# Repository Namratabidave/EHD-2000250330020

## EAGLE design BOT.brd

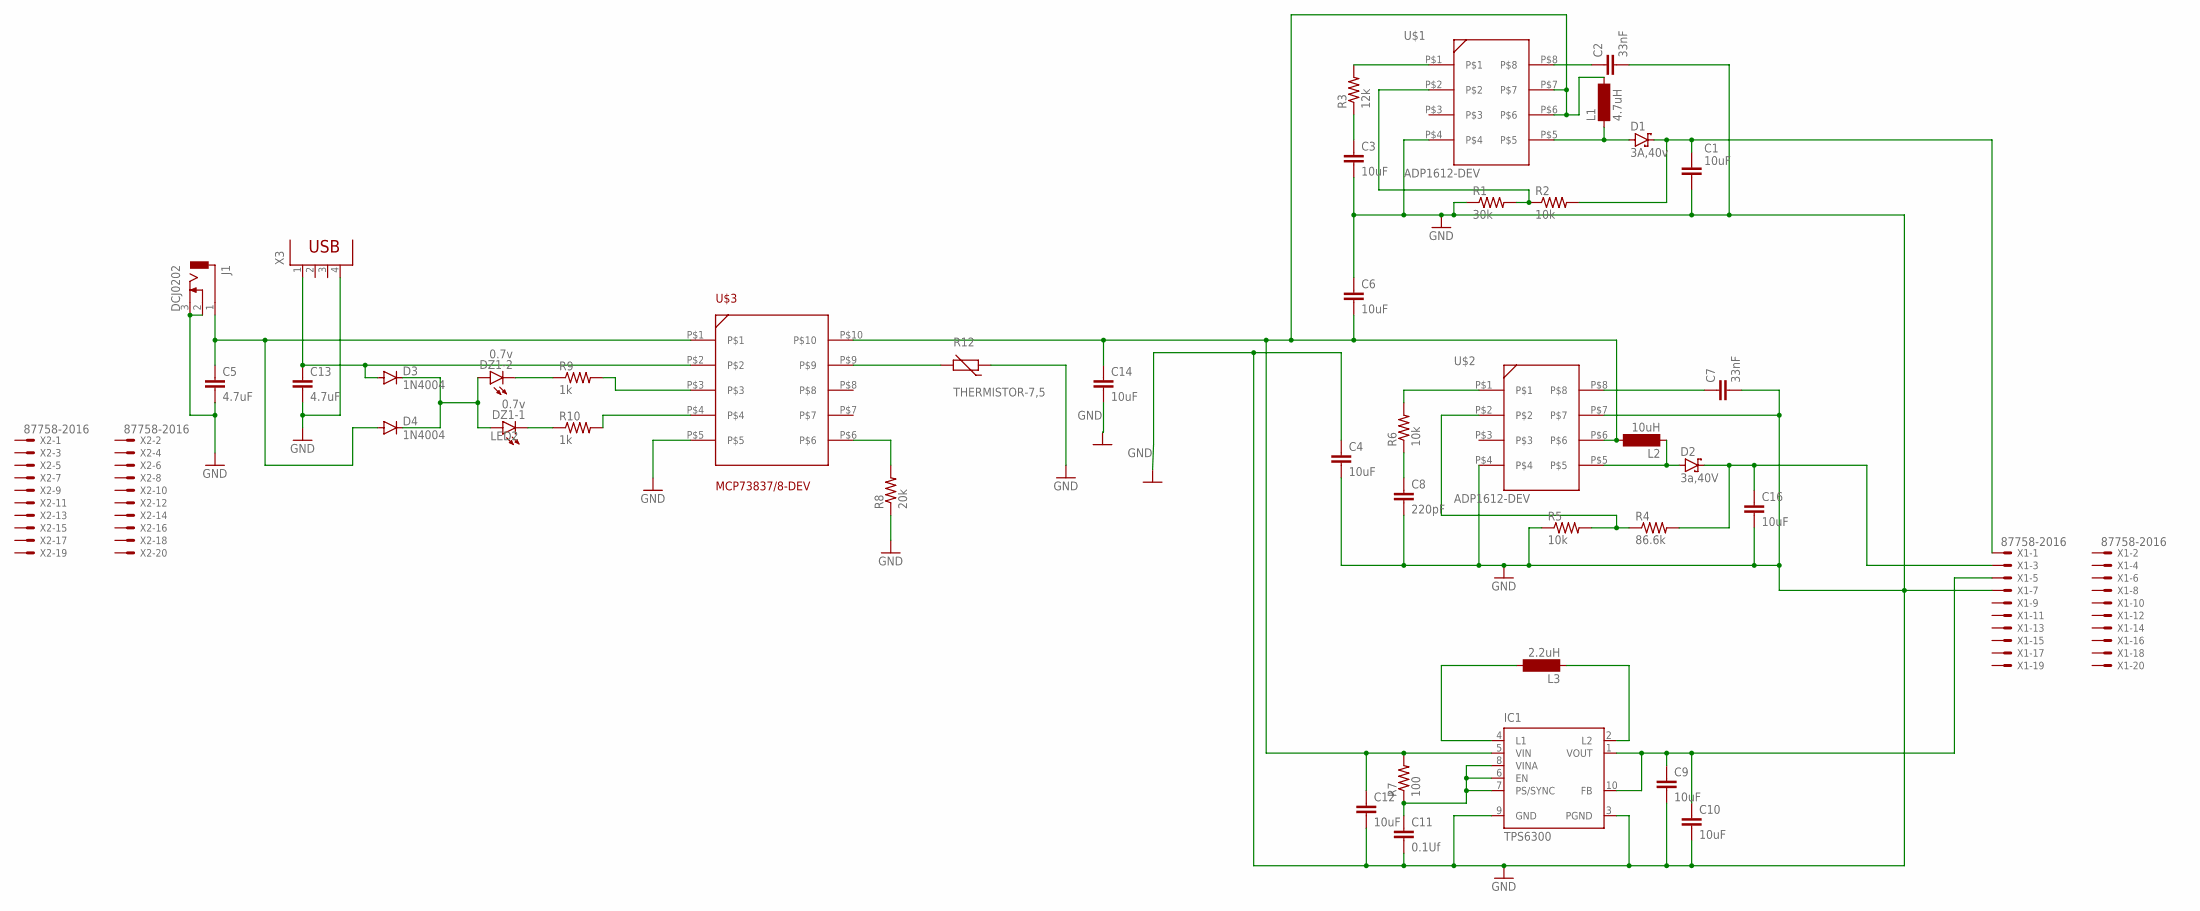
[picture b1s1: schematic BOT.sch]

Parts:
C2: 33nF; C2.5-2
C3, C6, C14: 10uF; C2.5-2
C4, C9, C10, C12, C16: 10uF; C2.5-3
C5, C13: 4.7uF; C2.5-2
C7: 33nF; C2.5-3
C8: 220pF; C2.5-3
C11: 0.1Uf; C2.5-3
D1: 3A,40v; SOD323_ST
D2: 3a,40V; SOD323_ST
D3, D4: 1N4004; DO41-10
DZ1: 0.7v; LZR182
IC1: TPS6300; DRC-S-PVSON-N10
J1: DCJ0202
L1: 4.7uH; SD8
L2: 10uH; SD8
L3: 2.2uH; SD8
R1: 30k; 0204/5
R2, R5, R6: 10k; 0204/5
R3: 12k; 0204/5
R4: 86.6k; 0204/5
R7: 100; 0204/5
R8: 20k; 0204/5
R9, R10: 1k; 0204/5
R12: THERMISTOR-7,5; R-7,5
U$1, U$2: ADP1612-DEV; MSOP-ADP1612
U$3: MCP73837/8-DEV; MSOP-MCP73837/8
X1, X2: 87758-2016
X3: PN87520

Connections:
GND: C2.2, C3.2, C4.1, C4.2, C5.2, C6.1, C7.2, C8.2, C9.2, C10.2, C11.2, C12.2, C13.2, C14.2, C16.2, IC1.3 (PGND), IC1.9 (GND), J1.2, J1.3, R1.1, R5.1, R8.1, R12.1, U$1.P$4, U$2.P$4, U$2.P$7, U$3.P$5, X1.7, X3.4
LED2: D3.C, D4.C, DZ1.A1 (A), DZ1.A2 (A)
unnamed: R3.2, U$1.P$1
unnamed: C3.1, R3.1
unnamed: C2.1, U$1.P$8
unnamed: R8.2, U$3.P$6
unnamed: D1.A, L1.1, U$1.P$5
unnamed: R1.2, R2.1, U$1.P$2
unnamed: R6.2, U$2.P$1
unnamed: D1.C, R2.2, X1.1
unnamed: C8.1, R6.1
unnamed: R9.2, U$3.P$3
unnamed: D2.A, L2.1, U$2.P$5
unnamed: IC1.4 (L1), L3.2
unnamed: C7.1, U$2.P$8
unnamed: R4.1, R5.2, U$2.P$2
unnamed: C16.1, D2.C, R4.2, X1.3
unnamed: IC1.2 (L2), L3.1
unnamed: C9.1, C10.1, IC1.1 (VOUT), IC1.10 (FB), X1.5
unnamed: C6.2, C12.1, C14.1, IC1.5 (VIN), L1.2, L2.2, R7.2, U$1.P$6, U$1.P$7, U$2.P$6, U$3.P$10
unnamed: C11.1, IC1.6 (EN), IC1.7 (PS/SYNC), IC1.8 (VINA), R7.1
unnamed: R12.2, U$3.P$9
unnamed: DZ1.K2 (C), R9.1
unnamed: DZ1.K1 (C), R10.1
unnamed: C5.1, D4.A, J1.1, U$3.P$1
unnamed: R10.2, U$3.P$4
unnamed: C13.1, D3.A, U$3.P$2, X3.1

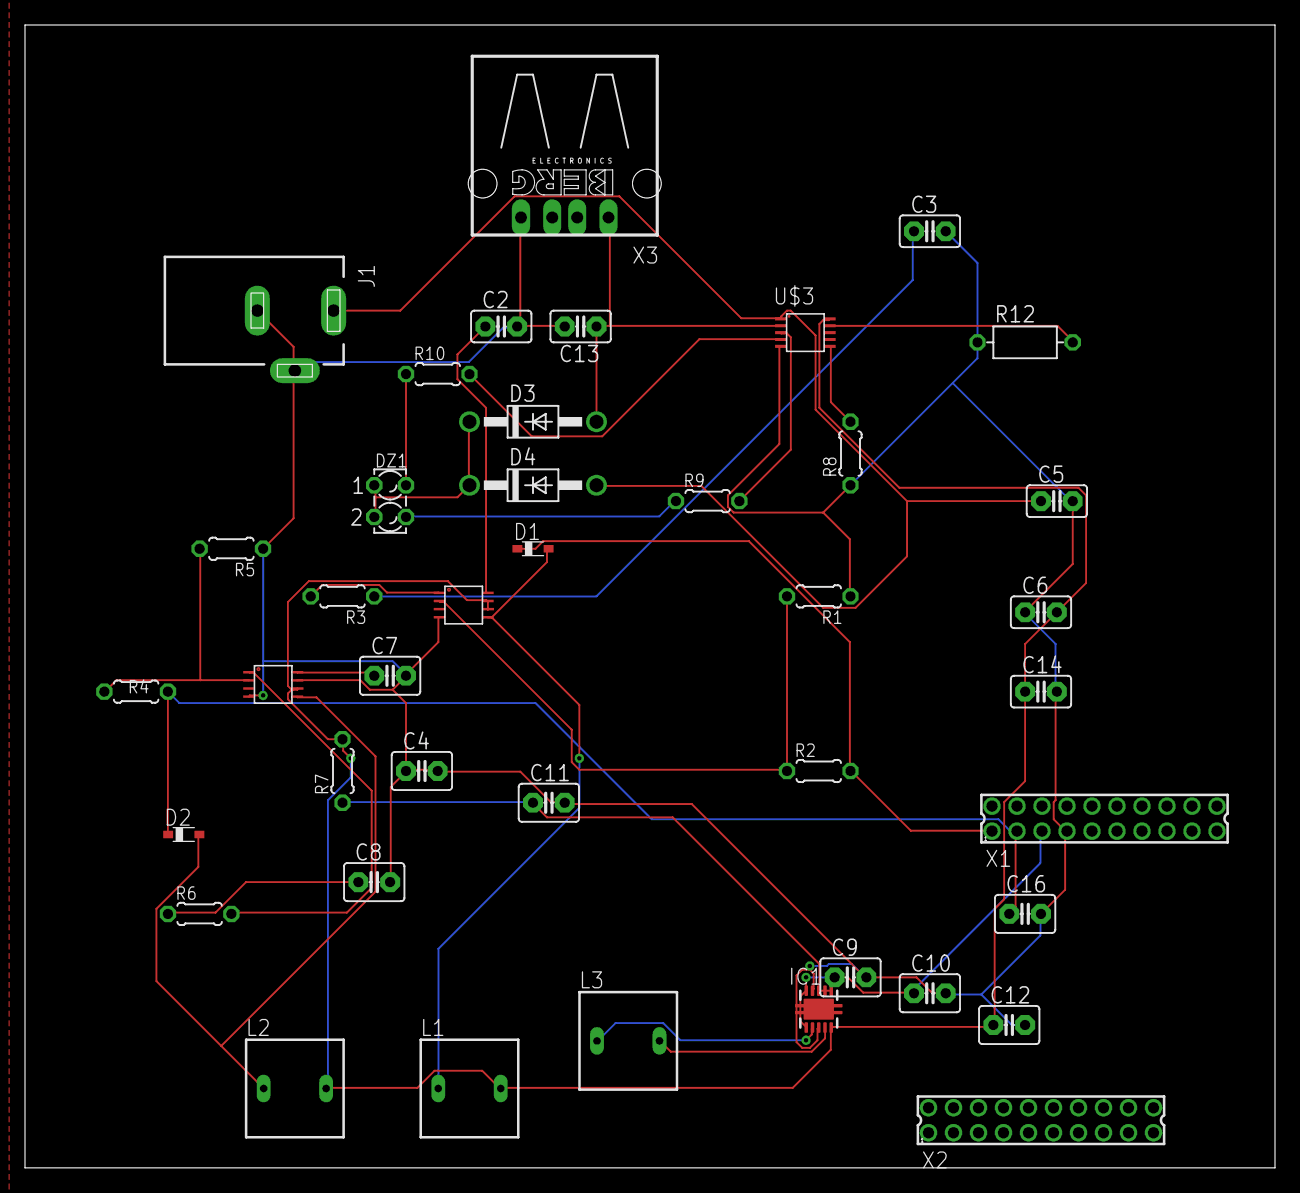
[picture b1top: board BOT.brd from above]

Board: 2 copper layers, 100.0 x 91.4 mm, 41 parts (0 on the bottom side), 27 nets.

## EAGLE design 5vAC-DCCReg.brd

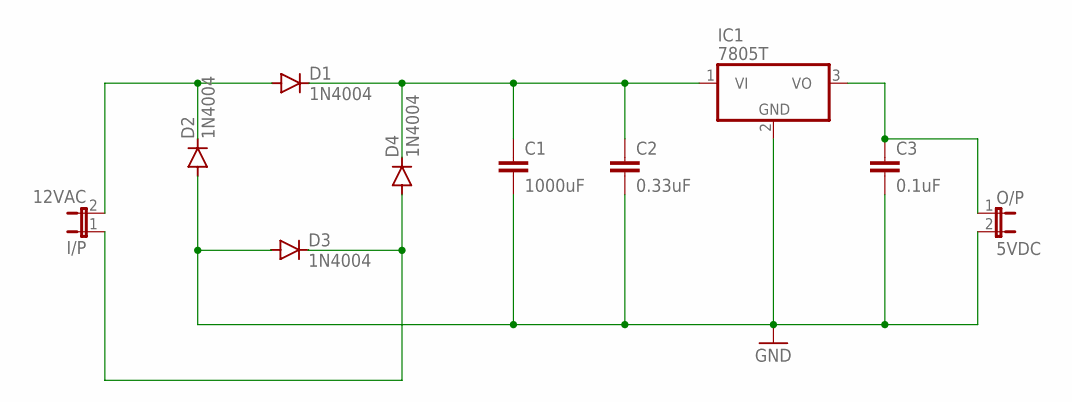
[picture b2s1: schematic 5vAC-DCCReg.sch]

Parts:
C1: 1000uF; C2.5-3
C2: 0.33uF; C2.5-3
C3: 0.1uF; C2.5-3
D1, D2, D3, D4: 1N4004; DO41-10
I/P: 12VAC; JP1
IC1: 7805T; TO220H
O/P: 5VDC; JP1

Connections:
GND: C1.2, C2.2, C3.2, D2.A, D3.A, IC1.2 (GND), O/P.2
unnamed: D1.A, D2.C, I/P.2
unnamed: C1.1, C2.1, D1.C, D4.C, IC1.1 (VI)
unnamed: D3.C, D4.A, I/P.1
unnamed: C3.1, IC1.3 (VO), O/P.1

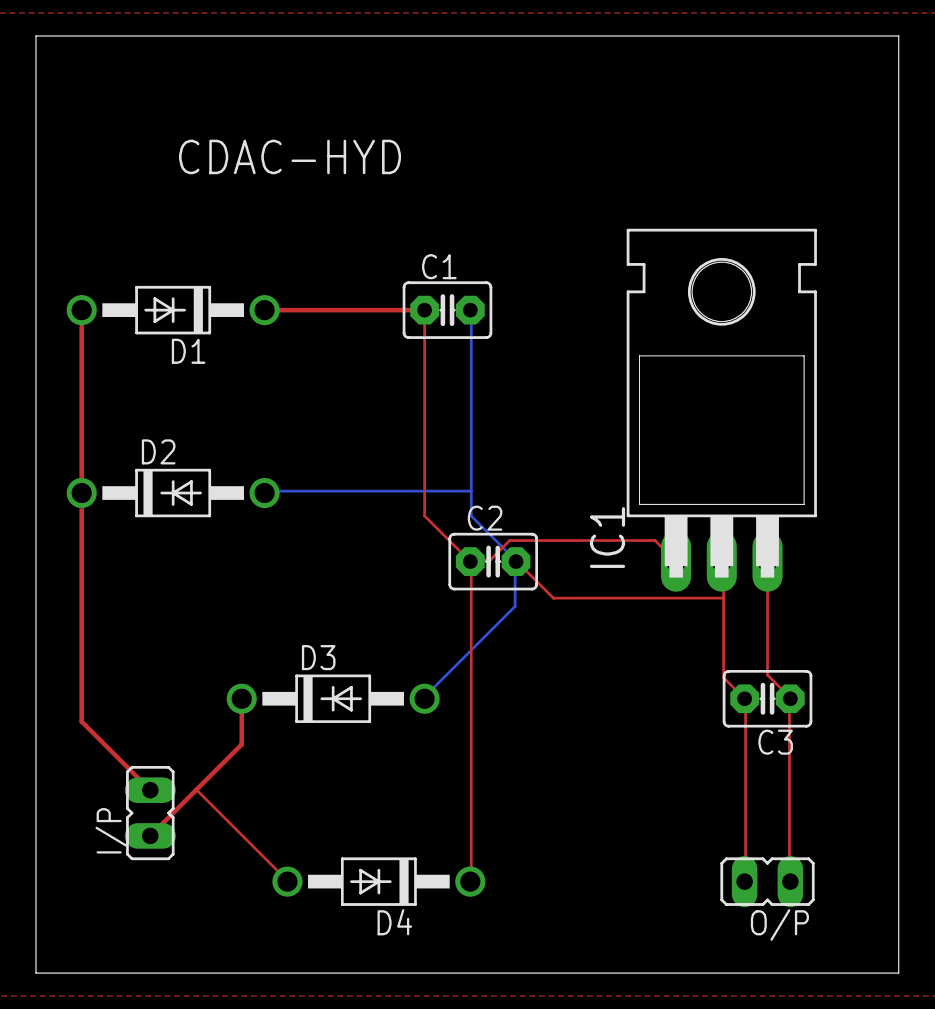
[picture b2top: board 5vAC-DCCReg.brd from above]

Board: 2 copper layers, 47.9 x 52.1 mm, 10 parts (0 on the bottom side), 5 nets.

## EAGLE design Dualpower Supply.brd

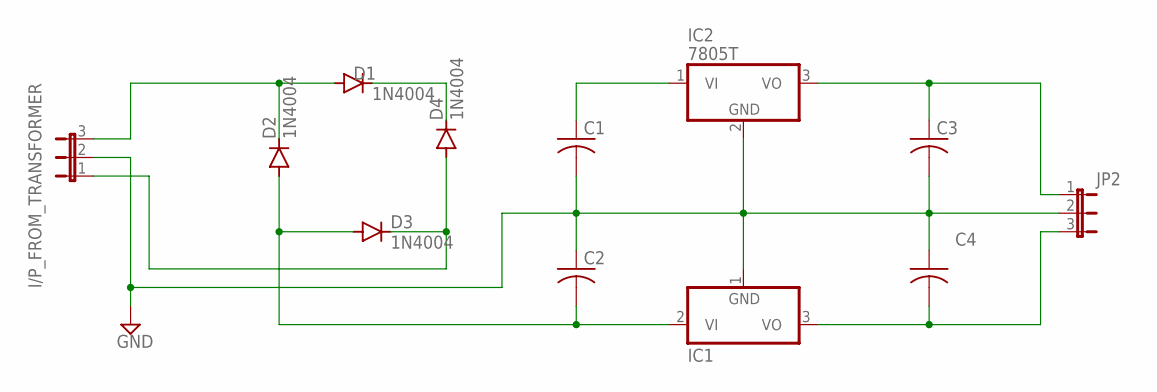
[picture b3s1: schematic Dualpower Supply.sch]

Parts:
C1, C2, C3, C4: C-US025-024X044; C025-024X044
D1, D2, D3, D4: 1N4004; DO41-10
I/P_FROM_TRANSFORMER: JP2E; JP2
IC1: 7905T; TO220H
IC2: 7805T; TO220H
JP2: JP2E; JP2

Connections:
GND: C1.2, C2.1, C3.2, C4.1, I/P_FROM_TRANSFORMER.2, IC1.1 (GND), IC2.2 (GND), JP2.2
unnamed: D1.A, D2.C, I/P_FROM_TRANSFORMER.3
unnamed: D1.C, D4.C
unnamed: D3.C, D4.A, I/P_FROM_TRANSFORMER.1
unnamed: C2.2, D2.A, D3.A, IC1.2 (VI)
unnamed: C1.1, IC2.1 (VI)
unnamed: C3.1, IC2.3 (VO), JP2.1
unnamed: C4.2, IC1.3 (VO), JP2.3

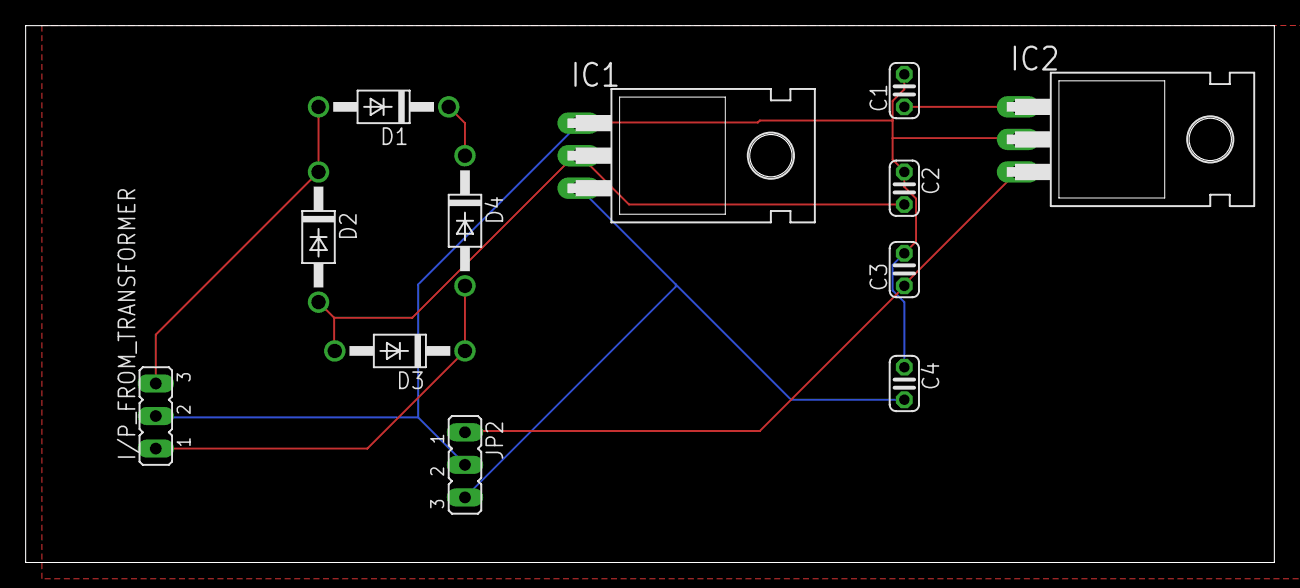
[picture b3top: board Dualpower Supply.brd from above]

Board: 2 copper layers, 97.5 x 41.9 mm, 13 parts (0 on the bottom side), 8 nets.

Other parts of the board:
U$1: 1N4001
